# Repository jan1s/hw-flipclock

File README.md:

# hw-flipclock

> :warning: **WARNING**: This project is totally untested so far.

This project is a stack-on PCB for typical 60-Pin flipdot panels.

## Render

## Schematic

## Disclaimer

THE HARDWARE DESIGN IS PROVIDED "AS IS", WITHOUT WARRANTY OF ANY KIND, EXPRESS OR IMPLIED, INCLUDING BUT NOT LIMITED TO THE WARRANTIES OF MERCHANTABILITY, FITNESS FOR A PARTICULAR PURPOSE AND NONINFRINGEMENT. IN NO EVENT SHALL THE AUTHORS OR COPYRIGHT HOLDERS BE LIABLE FOR ANY CLAIM, DAMAGES OR OTHER LIABILITY, WHETHER IN AN ACTION OF CONTRACT, TORT OR OTHERWISE, ARISING FROM, OUT OF OR IN CONNECTION WITH THE HARDWARE DESIGN OR THE USE OR OTHER DEALINGS IN THE HARDWARE DESIGN.

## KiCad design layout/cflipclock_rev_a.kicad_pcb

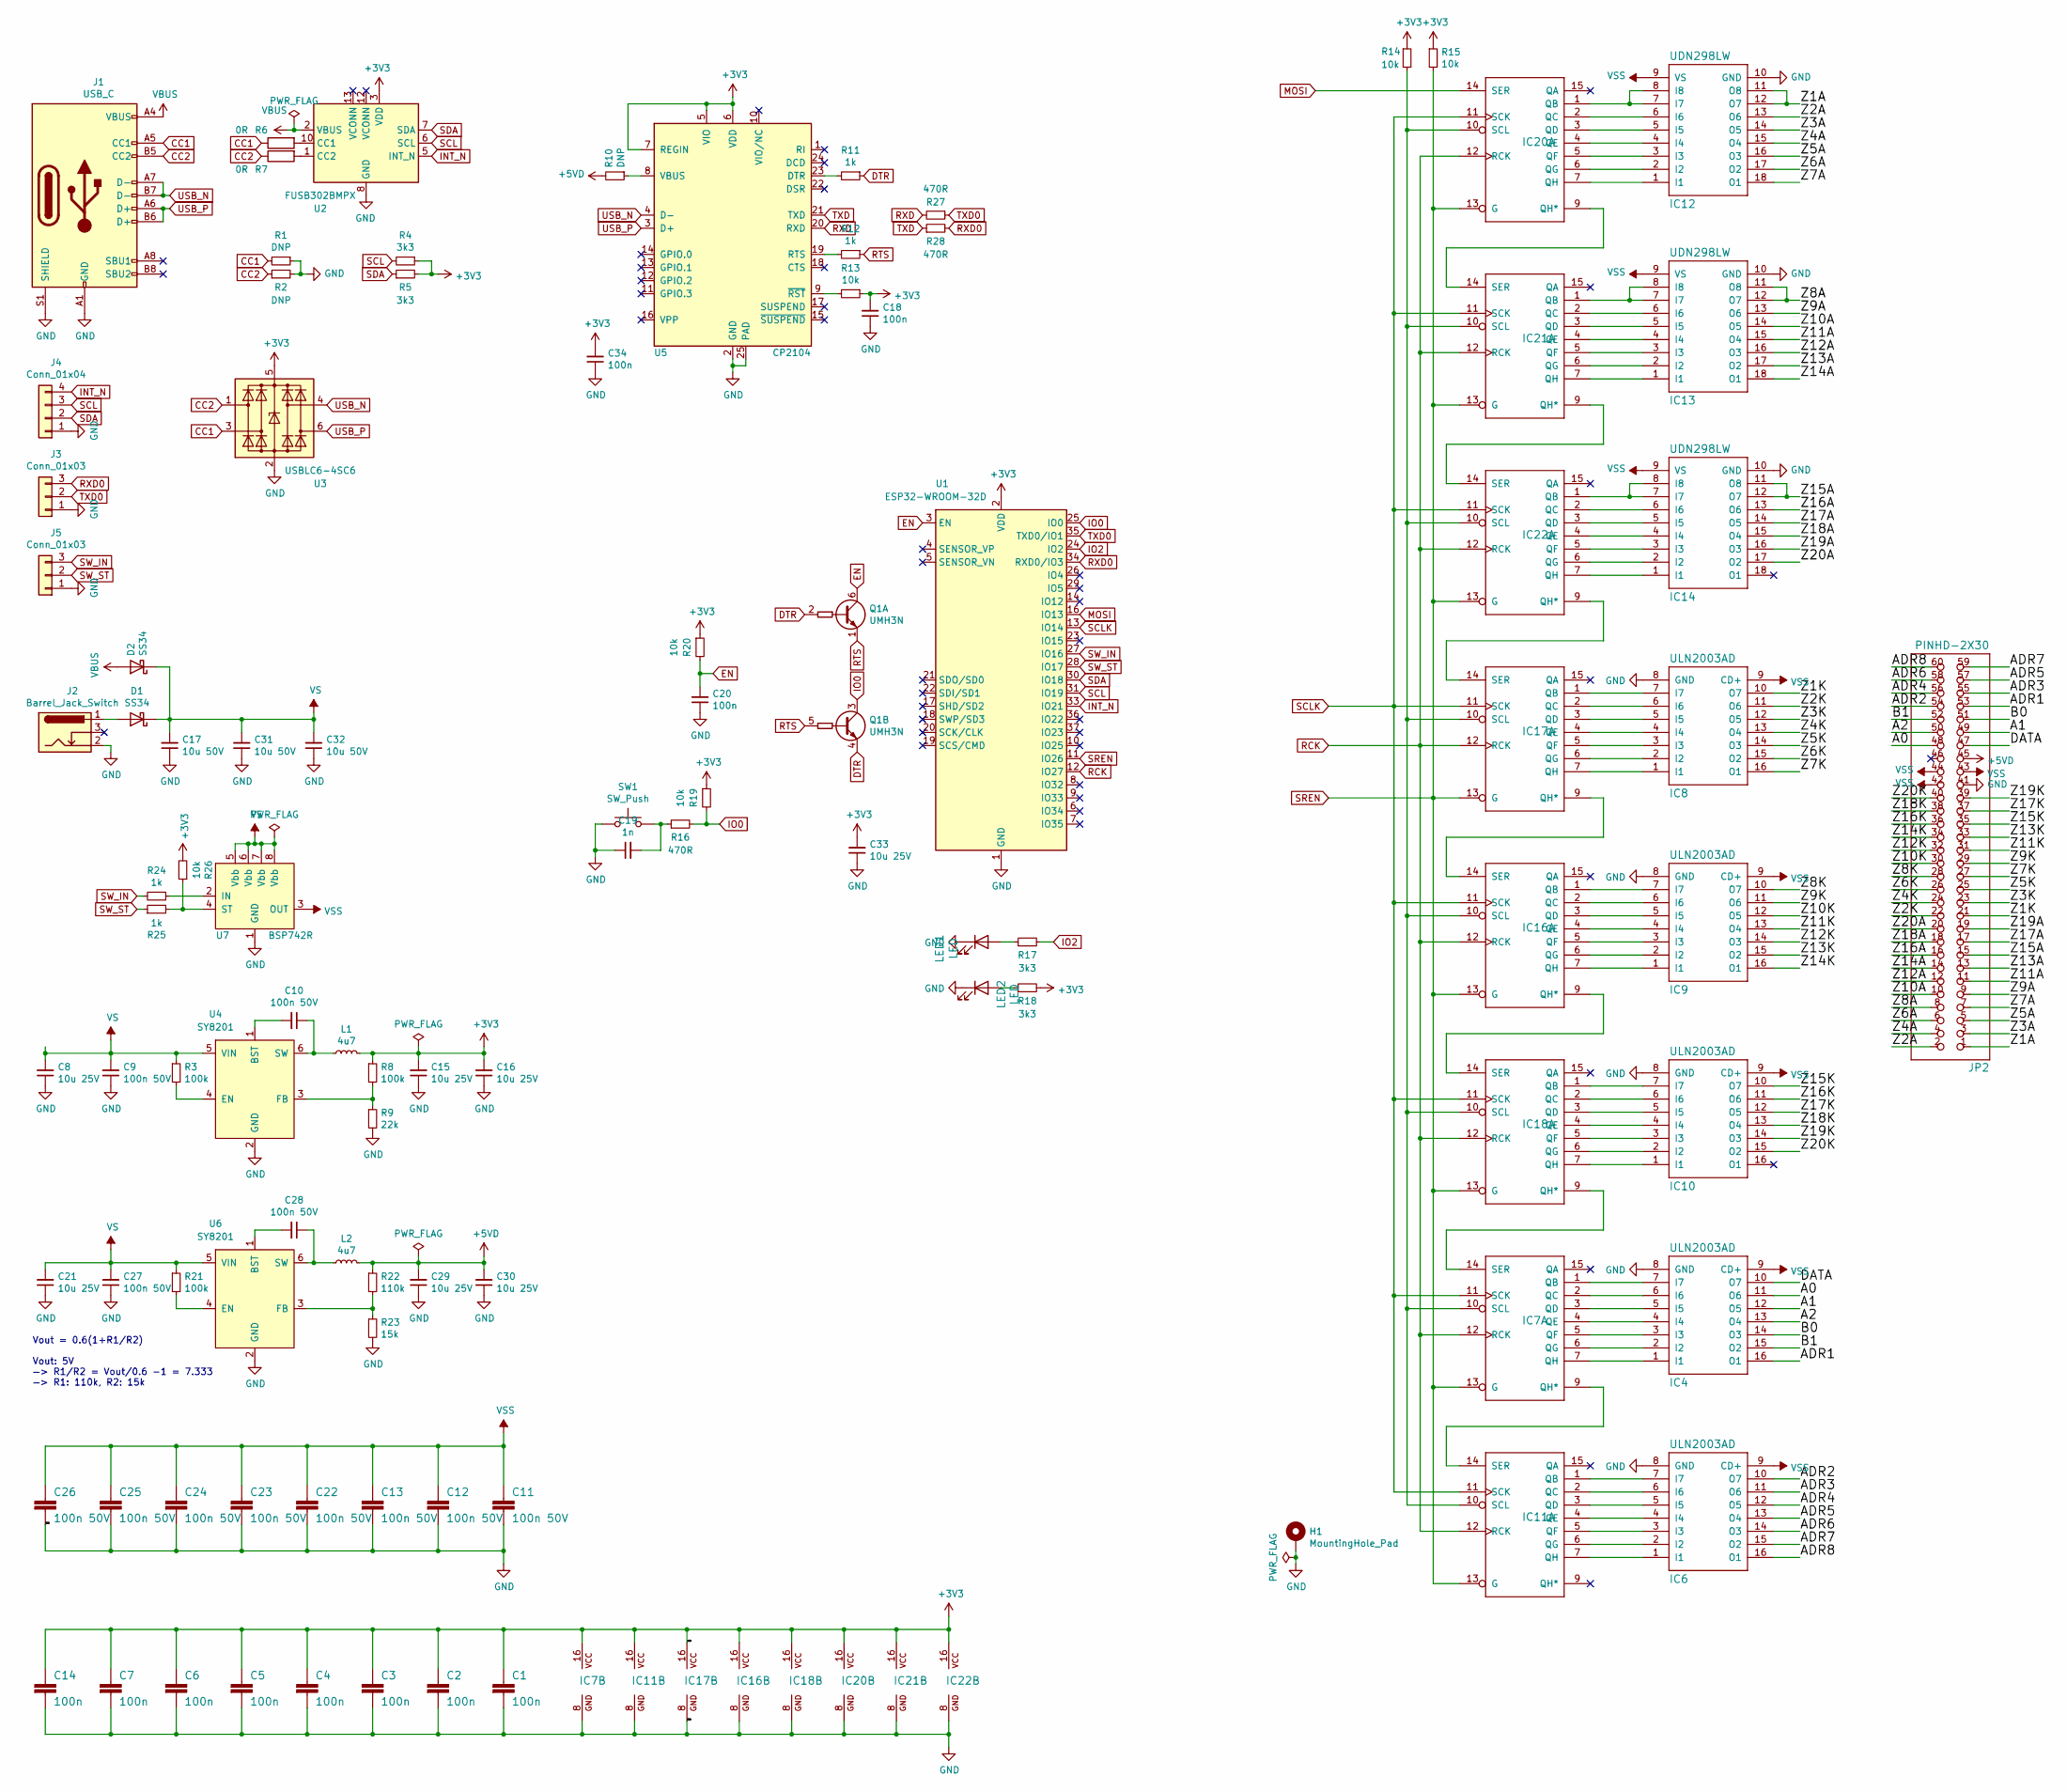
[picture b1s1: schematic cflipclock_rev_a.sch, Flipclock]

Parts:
C1, C2, C3, C4, C5, C6, C7, C14, C18, C20, C34: 100n; C_0402_1005Metric; LCSC C1525
C8, C15, C16, C21, C29, C30, C33: 10u 25V; C_0805_2012Metric; LCSC C15850
C9, C10, C11, C12, C13, C22, C23, C24, C25, C26, C27, C28: 100n 50V; C_0603_1608Metric; LCSC C14663
C17, C31, C32: 10u 50V; C_1206_3216Metric; LCSC C13585
C19: 1n; C_0402_1005Metric; LCSC C1523
D1, D2: SS34; D_SMA; LCSC C8678
H1: MountingHole_Pad; MountingHole_3.2mm_M3_Pad_Via
IC4, IC6, IC8, IC9, IC10: ULN2003AD; TSSOP-16_4.4x5mm_P0.65mm; LCSC C126289
IC7, IC11, IC16, IC17, IC18, IC20, IC21, IC22: 74595D; TSSOP-16_4.4x5mm_P0.65mm; LCSC C273642
IC12, IC13, IC14: UDN298LW; SOIC-18W_7.5x11.6mm_P1.27mm; LCSC C699444
J1: USB_C; USB_C_Receptacle_HRO_TYPE-C-31-M-12
J2: Barrel_Jack_Switch; BarrelJack_Horizontal
J3, J5: Conn_01x03; PinHeader_1x03_P2.54mm_Vertical
J4: Conn_01x04; PinHeader_1x04_P2.54mm_Vertical
JP2: PINHD-2X30; 2X30
L1, L2: 4u7; L_1210_3225Metric; LCSC C86070
LED1: LED; LED_0603_1608Metric; LCSC C2286
LED2: LED; LED_0603_1608Metric; LCSC C2290
Q1: UMH3N; SOT-363_SC-70-6
R1, R2, R10: DNP; R_0402_1005Metric
R3, R8, R21: 100k; R_0402_1005Metric; LCSC C25741
R4, R5, R17, R18: 3k3; R_0402_1005Metric; LCSC C25890
R6, R7: 0R; R_0402_1005Metric; LCSC C17168
R9: 22k; R_0402_1005Metric; LCSC C25768
R11, R12, R24, R25: 1k; R_0402_1005Metric; LCSC C11702
R13, R14, R15, R19, R20, R26: 10k; R_0402_1005Metric; LCSC C25744
R16, R27, R28: 470R; R_0402_1005Metric; LCSC C25117
R22: 110k; R_0402_1005Metric; LCSC C25745
R23: 15k; R_0402_1005Metric; LCSC C25756
SW1: SW_Push; SW_SPST_PTS810
U1: ESP32-WROOM-32D; ESP32-WROOM-32
U2: FUSB302BMPX; WQFN-14-1EP_2.5x2.5mm_P0.5mm_EP1.45x1.45mm; LCSC C442699
U3: USBLC6-4SC6; SOT-23-6; LCSC C435848
U4, U6: SY8201; SOT-23-6; LCSC C108052
U5: CP2104; QFN-24-1EP_4x4mm_P0.5mm_EP2.6x2.6mm; LCSC C47742
U7: BSP742R; SOIC-8_3.9x4.9mm_P1.27mm; LCSC C111024

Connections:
+3V3: C1.1, C2.1, C3.1, C4.1, C5.1, C6.1, C7.1, C14.1, C15.2, C16.2, C18.2, C33.2, C34.2, IC7.16 (VCC), IC11.16 (VCC), IC16.16 (VCC), IC17.16 (VCC), IC18.16 (VCC), IC20.16 (VCC), IC21.16 (VCC), IC22.16 (VCC), L1.2, R4.1, R5.2, R8.1, R13.1, R14.1, R15.1, R18.2, R19.1, R20.1, R26.2, U1.2 (VDD), U2.3 (VDD), U2.4 (VDD), U3.5 (VBUS), U5.5 (VIO), U5.6 (VDD), U5.7 (REGIN)
+5VD: C29.2, C30.2, JP2.45, L2.2, R10.2, R22.1
/A0: IC4.11 (O6), JP2.48
/A1: IC4.12 (O5), JP2.49
/A2: IC4.13 (O4), JP2.50
/ADR1: IC4.16 (O1), JP2.53
/ADR2: IC6.10 (O7), JP2.54
/ADR3: IC6.11 (O6), JP2.55
/ADR4: IC6.12 (O5), JP2.56
/ADR5: IC6.13 (O4), JP2.57
/ADR6: IC6.14 (O3), JP2.58
/ADR7: IC6.15 (O2), JP2.59
/ADR8: IC6.16 (O1), JP2.60
/B0: IC4.14 (O3), JP2.51
/B1: IC4.15 (O2), JP2.52
/DATA: IC4.10 (O7), JP2.47
/Z1A: IC12.11 (O8), IC12.12 (O7), JP2.1
/Z1K: IC8.10 (O7), JP2.21
/Z2A: IC12.13 (O6), JP2.2
/Z2K: IC8.11 (O6), JP2.22
/Z3A: IC12.14 (O5), JP2.3
/Z3K: IC8.12 (O5), JP2.23
/Z4A: IC12.15 (O4), JP2.4
/Z4K: IC8.13 (O4), JP2.24
/Z5A: IC12.16 (O3), JP2.5
/Z5K: IC8.14 (O3), JP2.25
/Z6A: IC12.17 (O2), JP2.6
/Z6K: IC8.15 (O2), JP2.26
/Z7A: IC12.18 (O1), JP2.7
/Z7K: IC8.16 (O1), JP2.27
/Z8A: IC13.11 (O8), IC13.12 (O7), JP2.8
/Z8K: IC9.10 (O7), JP2.28
/Z9A: IC13.13 (O6), JP2.9
/Z9K: IC9.11 (O6), JP2.29
/Z10A: IC13.14 (O5), JP2.10
/Z10K: IC9.12 (O5), JP2.30
/Z11A: IC13.15 (O4), JP2.11
/Z11K: IC9.13 (O4), JP2.31
/Z12A: IC13.16 (O3), JP2.12
/Z12K: IC9.14 (O3), JP2.32
/Z13A: IC13.17 (O2), JP2.13
/Z13K: IC9.15 (O2), JP2.33
/Z14A: IC13.18 (O1), JP2.14
/Z14K: IC9.16 (O1), JP2.34
/Z15A: IC14.11 (O8), IC14.12 (O7), JP2.15
/Z15K: IC10.10 (O7), JP2.35
/Z16A: IC14.13 (O6), JP2.16
/Z16K: IC10.11 (O6), JP2.36
/Z17A: IC14.14 (O5), JP2.17
/Z17K: IC10.12 (O5), JP2.37
/Z18A: IC14.15 (O4), JP2.18
/Z18K: IC10.13 (O4), JP2.38
/Z19A: IC14.16 (O3), JP2.19
/Z19K: IC10.14 (O3), JP2.39
/Z20A: IC14.17 (O2), JP2.20
/Z20K: IC10.15 (O2), JP2.40
CC1: J1.A5 (CC1), R1.2, R6.1, U3.3 (I/O2)
CC2: J1.B5 (CC2), R2.1, R7.1, U3.1 (I/O1)
DTR: Q1.2 (B1), Q1.4 (E2), R11.1
EN: C20.2, Q1.6 (C1), R20.2, U1.3 (EN)
GND: C1.2, C2.2, C3.2, C4.2, C5.2, C6.2, C7.2, C8.1, C9.1, C11.2, C12.2, C13.2, C14.2, C15.1, C16.1, C17.1, C18.1, C19.1, C20.1, C21.1, C22.2, C23.2, C24.2, C25.2, C26.2, C27.1, C29.1, C30.1, C31.1, C32.1, C33.1, C34.1, H1.1, IC4.8 (GND), IC6.8 (GND), IC7.8 (GND), IC8.8 (GND), IC9.8 (GND), IC10.8 (GND), IC11.8 (GND), IC12.10 (GND), IC13.10 (GND), IC14.10 (GND), IC16.8 (GND), IC17.8 (GND), IC18.8 (GND), IC20.8 (GND), IC21.8 (GND), IC22.8 (GND), J1.A1 (GND), J1.A12 (GND), J1.B1 (GND), J1.B12 (GND), J1.S1 (SHIELD), J2.2, J3.1, J4.1, J5.1, JP2.41, LED1.1 (K), LED2.1 (K), R1.1, R2.2, R9.2, R23.2, SW1.1, U1.1 (GND), U1.15 (GND), U1.38 (GND), U1.39 (GND), U2.8 (GND), U2.9 (GND), U2.15 (GND), U3.2 (GND), U4.2 (GND), U5.2 (GND), U5.25 (PAD), U6.2 (GND), U7.1 (GND)
INT_N: J4.4, U1.33 (IO21), U2.5 (INT_N)
IO0: Q1.3 (C2), R16.2, R19.2, U1.25 (IO0)
IO2: R17.2, U1.24 (IO2)
MOSI: IC20.14 (SER), U1.16 (IO13)
unnamed: C10.1, L1.1, U4.6 (SW)
unnamed: C10.2, U4.1 (BST)
unnamed: C19.2, R16.1, SW1.2
unnamed: C28.1, L2.1, U6.6 (SW)
unnamed: C28.2, U6.1 (BST)
unnamed: D1.2 (A), J2.1
unnamed: IC4.1 (I1), IC7.7 (QH)
unnamed: IC4.2 (I2), IC7.6 (QG)
unnamed: IC4.3 (I3), IC7.5 (QF)
unnamed: IC4.4 (I4), IC7.4 (QE)
unnamed: IC4.5 (I5), IC7.3 (QD)
unnamed: IC4.6 (I6), IC7.2 (QC)
unnamed: IC4.7 (I7), IC7.1 (QB)
unnamed: IC10.1 (I1), IC18.7 (QH)
unnamed: IC10.2 (I2), IC18.6 (QG)
unnamed: IC10.3 (I3), IC18.5 (QF)
unnamed: IC10.4 (I4), IC18.4 (QE)
unnamed: IC10.5 (I5), IC18.3 (QD)
unnamed: IC10.6 (I6), IC18.2 (QC)
unnamed: IC10.7 (I7), IC18.1 (QB)
unnamed: IC6.7 (I7), IC11.1 (QB)
unnamed: IC6.6 (I6), IC11.2 (QC)
unnamed: IC6.5 (I5), IC11.3 (QD)
unnamed: IC6.4 (I4), IC11.4 (QE)
unnamed: IC6.3 (I3), IC11.5 (QF)
unnamed: IC6.2 (I2), IC11.6 (QG)
unnamed: IC6.1 (I1), IC11.7 (QH)
unnamed: IC7.10 (SCL), IC11.10 (SCL), IC16.10 (SCL), IC17.10 (SCL), IC18.10 (SCL), IC20.10 (SCL), IC21.10 (SCL), IC22.10 (SCL), R14.2
unnamed: IC7.9 (QH*), IC11.14 (SER)
unnamed: IC12.1 (I1), IC20.7 (QH)
unnamed: IC12.2 (I2), IC20.6 (QG)
unnamed: IC12.3 (I3), IC20.5 (QF)
unnamed: IC12.4 (I4), IC20.4 (QE)
unnamed: IC12.5 (I5), IC20.3 (QD)
unnamed: IC12.6 (I6), IC20.2 (QC)
unnamed: IC12.7 (I7), IC12.8 (I8), IC20.1 (QB)
unnamed: IC13.1 (I1), IC21.7 (QH)
unnamed: IC13.2 (I2), IC21.6 (QG)
unnamed: IC13.3 (I3), IC21.5 (QF)
unnamed: IC13.4 (I4), IC21.4 (QE)
unnamed: IC13.5 (I5), IC21.3 (QD)
unnamed: IC13.6 (I6), IC21.2 (QC)
unnamed: IC13.7 (I7), IC13.8 (I8), IC21.1 (QB)
unnamed: IC14.1 (I1), IC22.7 (QH)
unnamed: IC14.2 (I2), IC22.6 (QG)
unnamed: IC14.3 (I3), IC22.5 (QF)
unnamed: IC14.4 (I4), IC22.4 (QE)
unnamed: IC14.5 (I5), IC22.3 (QD)
unnamed: IC14.6 (I6), IC22.2 (QC)
unnamed: IC14.7 (I7), IC14.8 (I8), IC22.1 (QB)
unnamed: IC9.7 (I7), IC16.1 (QB)
unnamed: IC9.6 (I6), IC16.2 (QC)
unnamed: IC9.5 (I5), IC16.3 (QD)
unnamed: IC9.4 (I4), IC16.4 (QE)
unnamed: IC9.3 (I3), IC16.5 (QF)
unnamed: IC9.2 (I2), IC16.6 (QG)
unnamed: IC9.1 (I1), IC16.7 (QH)
unnamed: IC16.9 (QH*), IC18.14 (SER)
unnamed: IC16.14 (SER), IC17.9 (QH*)
unnamed: IC8.7 (I7), IC17.1 (QB)
unnamed: IC8.6 (I6), IC17.2 (QC)
unnamed: IC8.5 (I5), IC17.3 (QD)
unnamed: IC8.4 (I4), IC17.4 (QE)
unnamed: IC8.3 (I3), IC17.5 (QF)
unnamed: IC8.2 (I2), IC17.6 (QG)
unnamed: IC8.1 (I1), IC17.7 (QH)
unnamed: IC17.14 (SER), IC22.9 (QH*)
unnamed: IC7.14 (SER), IC18.9 (QH*)
unnamed: IC20.9 (QH*), IC21.14 (SER)
unnamed: IC21.9 (QH*), IC22.14 (SER)
unnamed: LED1.2 (A), R17.1
unnamed: LED2.2 (A), R18.1
unnamed: R3.2, U4.4 (EN)
unnamed: R6.2, U2.10 (CC1), U2.11 (CC1)
unnamed: R7.2, U2.1 (CC2), U2.14 (CC2)
unnamed: R8.2, R9.1, U4.3 (FB)
unnamed: R11.2, U5.23 (DTR)
unnamed: R12.2, U5.19 (RTS)
unnamed: R13.2, U5.9 (~RST)
unnamed: R21.2, U6.4 (EN)
unnamed: R22.2, R23.1, U6.3 (FB)
unnamed: R24.1, U7.2 (IN)
unnamed: R25.2, R26.1, U7.4 (ST)
RCK: IC7.12 (RCK), IC11.12 (RCK), IC16.12 (RCK), IC17.12 (RCK), IC18.12 (RCK), IC20.12 (RCK), IC21.12 (RCK), IC22.12 (RCK), U1.12 (IO27)
RTS: Q1.1 (E1), Q1.5 (B2), R12.1
RXD: R27.2, U5.20 (RXD)
RXD0: J3.3, R28.2, U1.34 (RXD0/IO3)
SCL: J4.3, R4.2, U1.31 (IO19), U2.6 (SCL)
SCLK: IC7.11 (SCK), IC11.11 (SCK), IC16.11 (SCK), IC17.11 (SCK), IC18.11 (SCK), IC20.11 (SCK), IC21.11 (SCK), IC22.11 (SCK), U1.13 (IO14)
SDA: J4.2, R5.1, U1.30 (IO18), U2.7 (SDA)
SREN: IC7.13 (G), IC11.13 (G), IC16.13 (G), IC17.13 (G), IC18.13 (G), IC20.13 (G), IC21.13 (G), IC22.13 (G), R15.2, U1.11 (IO26)
SW_IN: J5.3, R24.2, U1.27 (IO16)
SW_ST: J5.2, R25.1, U1.28 (IO17)
TXD: R28.1, U5.21 (TXD)
TXD0: J3.2, R27.1, U1.35 (TXD0/IO1)
USB_N: J1.A7 (D-), J1.B7 (D-), U3.4 (I/O3), U5.4 (D-)
USB_P: J1.A6 (D+), J1.B6 (D+), U3.6 (I/O4), U5.3 (D+)
VBUS: D2.2 (A), J1.A4 (VBUS), J1.A9 (VBUS), J1.B4 (VBUS), J1.B9 (VBUS), U2.2 (VBUS)
VBUS_SENSE: R10.1, U5.8 (VBUS)
VS: C8.2, C9.2, C17.2, C21.2, C27.2, C31.2, C32.2, D1.1 (K), D2.1 (K), R3.1, R21.1, U4.5 (VIN), U6.5 (VIN), U7.5 (Vbb), U7.6 (Vbb), U7.7 (Vbb), U7.8 (Vbb)
VSS: C11.1, C12.1, C13.1, C22.1, C23.1, C24.1, C25.1, C26.1, IC4.9 (CD+), IC6.9 (CD+), IC8.9 (CD+), IC9.9 (CD+), IC10.9 (CD+), IC12.9 (VS), IC13.9 (VS), IC14.9 (VS), JP2.42, JP2.43, JP2.44, U7.3 (OUT)

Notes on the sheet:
Vout = 0.6(1+R1/R2) Vout: 5V —> R1/R2 = Vout/0.6 -1 = 7.333 —> R1: 110k, R2: 15k

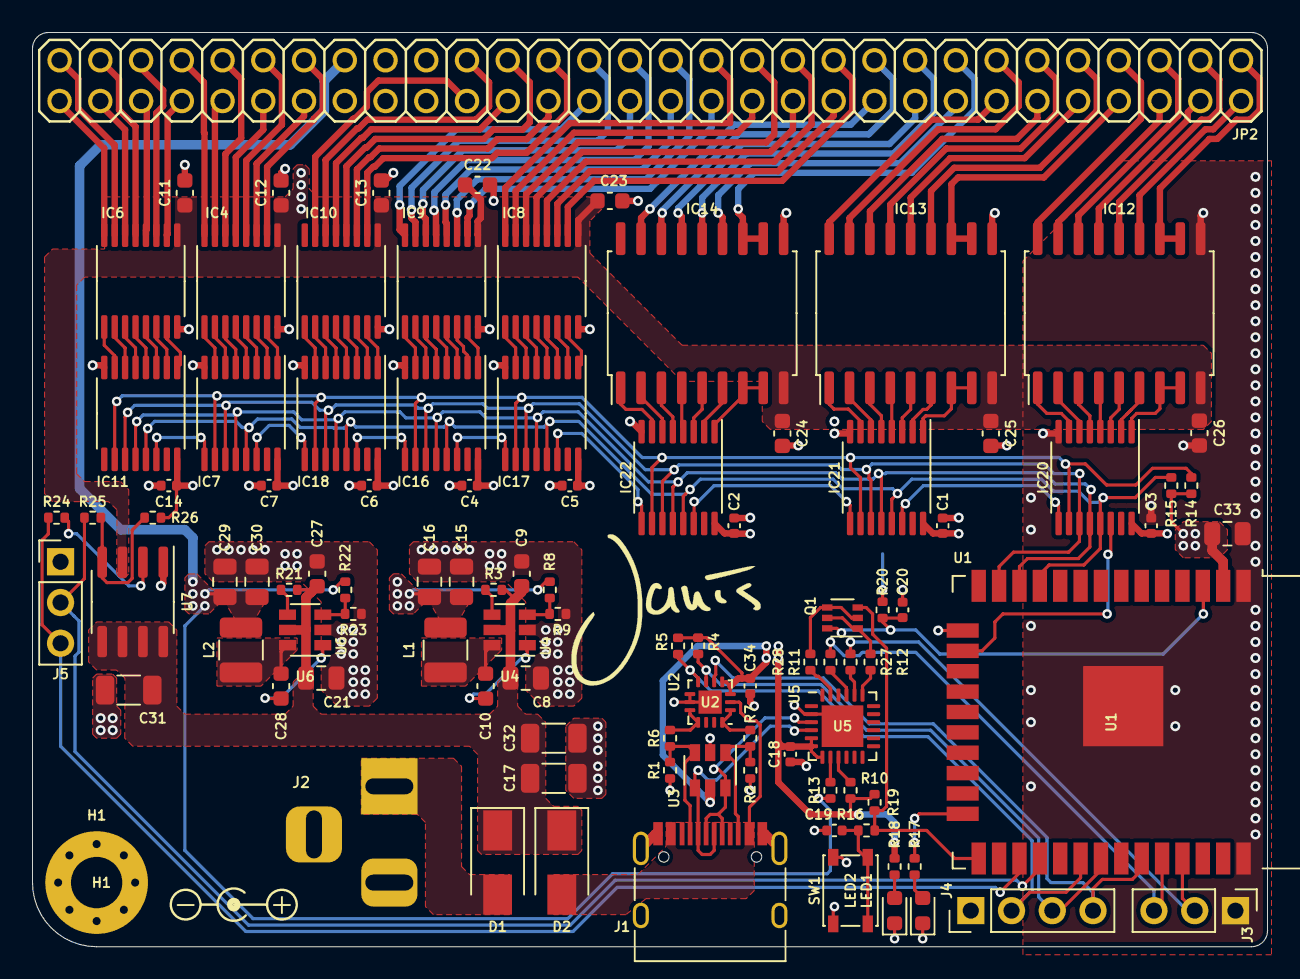
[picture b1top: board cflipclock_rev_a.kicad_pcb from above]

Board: 4 copper layers, 77.0 x 57.0 mm, 101 parts (0 on the bottom side), 166 nets.

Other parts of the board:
QR*****: https://janis.xyz; QR_janis.xyz_0.75

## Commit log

2021-03-17 Added schematic to readme
2021-03-17 Added render and disclaimer
2021-03-17 Image cropping
